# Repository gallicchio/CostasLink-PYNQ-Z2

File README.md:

# CostasLink-PYNQ-Z2

**A radio link whose reply is on its way 20 to 25 ns after the question arrives.**

An open-hardware 5 GHz transceiver board for a [PYNQ-Z2](http://www.pynq.io/boards.html), built for quantum
position verification: one station sends a challenge (a measurement basis), the other decides which of four it was
and answers, and the electronics add tens of nanoseconds to the light's travel time.

<p> </p>

Rev A on its PYNQ-Z2, and as drawn in KiCad: the front, with every jack labelled, and the back, with its
instructions. Click any image to open it at full size.

## What rev A measured

| | measured | how |
|---|---|---|
| **Turnaround**, antenna jack in to antenna jack out | **23 to 25 ns**; **20.4 to 20.8 ns** with lower thresholds | one board answering itself through a cable; no clock in the path |
| **Throughput**, idle to 1 of 4 | **2 million challenges a second** (4 Mbit/s), each answered and checked | two boards, both directions at once |
| | 4.2 million a second (8.3 Mbit/s) | one board, cabled to itself |
| **Errors**, cabled | **1 wrong in 155 billion** challenges, none missed | two boards, 21.6 hours |
| **Errors**, over the air | 1.5 in a million of 25.6 billion, in bursts | dishes across the lab one way, small antennas back, 3.6 hours untouched |
| **Idle to 1 of 8** (3 bits) | 105 million symbols, none wrong | two boards, cabled |
| **Round trip** | 120 ns on bench cables, 245 ns across the lab | one station's transmit edge to its decision on the other's reply |
| **Plain BPSK** | no error in 89 billion bits at 2 to 50 Mbaud; error-free to 20 Mbaud across the lab | one board over the air; two boards over the dishes |
| **Cost** | about $345 a board, assembled by JLCPCB | the estimate at the order, before duty and shipping; a PYNQ-Z2 is extra |

Every number is from the bench record: [`bringup/BRINGUP_LOG.md`](bringup/BRINGUP_LOG.md),
[`bringup/LATENCY.md`](bringup/LATENCY.md), [`bringup/FINDINGS.md`](bringup/FINDINGS.md).

## Photos

<table>
<tr>
<td width="50%"></td>
<td width="50%"></td>
</tr>
<tr>
<td>The two stations: a PYNQ-Z2 and a rev A board each.</td>
<td>Both stations running. Left scope: a challenge and its reply. Right scope: the received constellation, the idle and its messages.</td>
</tr>
<tr>
<td></td>
<td>One station at a demonstration in a lecture hall: a dish to send and a dish to receive, on carriers 600 MHz apart. The scope shows the live constellation.<br><br>All the photos are in <a href="photos/README.md"><code>photos/</code></a>.</td>
</tr>
</table>

## How it works

- **The transmitter never stops.** It idles on a plain carrier, so the receiver is always locked.
- **A message is one brief step** of that carrier to another point in the I/Q plane, then back.
- **A hardware Costas loop** keeps the receiver's oscillator on the carrier. It is slow (3 kHz) and the data never
  pass through it.
- **Five comparators decide**, straight off DC-coupled I and Q. No ADC, no matched filter, no symbol clock.
- **The FPGA's fast path has no clock**: comparator pins, a lookup table, transmit pins, 5 to 6 ns.

### Deciding before the symbol settles

- A receiver that samples a settled symbol waits about 1/bandwidth. This one waits for a threshold.
- With little noise the threshold sits close to the idle, and the rising edge crosses it early.
- Measured: lowering the thresholds from 0.4 to 0.2 of the step took 3 ns off the turnaround.
- The price: set too low, noise fires the comparators. In the two-board link, false events stopped at 0.4.

### Idle to 1 of N

| scheme | bits a symbol | tested |
|---|---|---|
| idle to 1 of 2 | 1 | cabled and over the air |
| **idle to 1 of 4** | 2 | cabled and over the air: most of the results above |
| **idle to 1 of 8** | 3 | cabled: 105 million symbols, none wrong |

**Eight is the most this board can do.** Two 2-bit resistor ladders give three levels on each axis, nine points:
the idle and eight messages. Four window comparators read each axis as low, middle or high. More messages need
more comparators and a linear transmitter ([`bringup/REVB.md`](bringup/REVB.md), row 42).

### Where a round trip's time goes

## What rev A does not do

| limit | detail |
|---|---|
| **5.8 GHz** | Designed for the 5.8 GHz band, but the receive gain falls off above 4.5 GHz and no link closed at 5.8. Every result here is on carriers between 4.4 and 5.5 GHz. |
| **A decoded message on a pin** | 85 to 105 ns one way, about 80 ns of it the gateware's clocked pipeline. The 20 to 25 ns is the clockless reply. |
| **One antenna** | Both directions at once need two antennas a board and carriers 600 MHz apart. |
| **Distance** | The longest paths so far: about 16 m of air across a lab, and a lecture hall. |
| **Lock** | Software restores a lost lock in 2 to 3 s. The thresholds are set for one signal level, within about 6 dB. |
| **1 of 8** | Tested over cables only. |

The full list, each with its measurement: [`bringup/REVB.md`](bringup/REVB.md).

## What is here

| path | what |
|---|---|
| [`hardware/`](hardware/) | the KiCad 10 project: 120 x 100 mm, 4 layers |
| [`mfg/release/`](mfg/release/) | what was uploaded to JLCPCB: Gerbers, BOM, placement |
| [`gateware/`](gateware/README.md) | the Verilog, the PYNQ overlay's build, the Python driver |
| [`bringup/`](bringup/README.md) | the bench programs, the log of every measurement, the list for rev B |
| [`gen/`](gen/), [`sim/`](sim/), [`tools/`](tools/) | the scripts that generate and check the design (`python3 build.py`) |
| [`docs/`](docs/) | the schematic as [PDF](docs/images/CostasLink-PYNQ-Z2_schematic.pdf), the studies, the figures |
| [`PLAN.md`](PLAN.md), [`BRINGUP.md`](BRINGUP.md) | the design and its reasons; the bring-up procedure |
| [`docs/DESIGN_STATUS.md`](docs/DESIGN_STATUS.md) | the design phase's own summary, step by step |
| [`design_review/`](design_review/README.md) | six reviews before the order, and [what was done about them](DESIGN_REVIEW_RESPONSE.md) |
| [`photos/`](photos/README.md) | the boards and the bench |

## How it was made

Jason Gallicchio designed this with Claude (Anthropic's Fable 5.1 and Opus 5.5, in Claude Code).

| | dates | days |
|---|---|---|
| Design, to the order at JLCPCB | 2026-10-09 to 2026-10-17 | 9 |
| Boards delivered | 2026-10-28 | |
| Bring-up and debugging | 2026-10-28 to 2026-11-11 | 15 |

Every prompt and every response is kept: [`CLAUDE_CODE_CHAT.md`](CLAUDE_CODE_CHAT.md) for the design,
[`bringup/CLAUDE_CODE_CHAT_BRINGUP.md`](bringup/CLAUDE_CODE_CHAT_BRINGUP.md) for the bench.

The board grew up in a private repository of the research group. Its commits are all here; vendor datasheets
are not. Commit hashes quoted in the documents are the old ones: [`docs/COMMIT_MAP.tsv`](docs/COMMIT_MAP.tsv).

## Before you transmit

This is an uncertified experimental radio. Check what you are licensed to radiate where you are, or work over
cables.

## Licence

Hardware under CERN-OHL-P-2.0, software under MIT: [`LICENSE`](LICENSE).

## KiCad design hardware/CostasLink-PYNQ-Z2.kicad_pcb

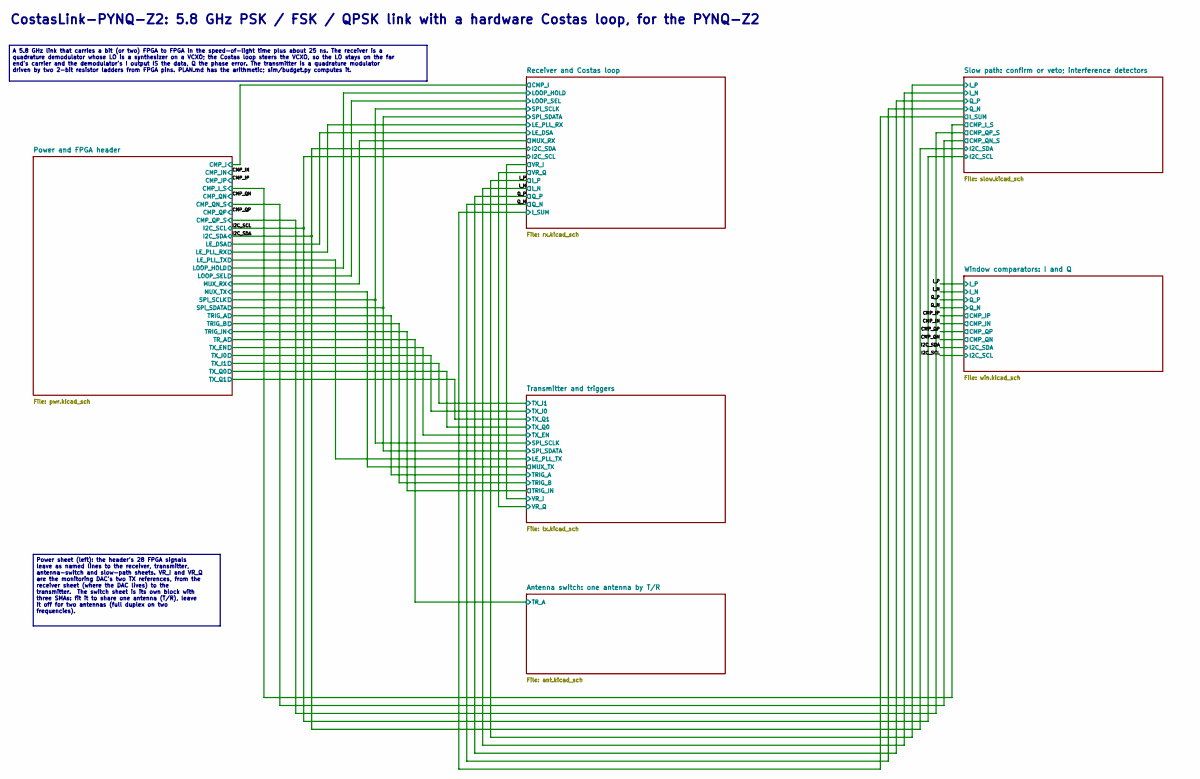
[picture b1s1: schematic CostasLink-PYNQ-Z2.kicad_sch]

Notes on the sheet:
CostasLink-PYNQ-Z2: 5.8 GHz PSK / FSK / QPSK link with a hardware Costas loop, for the PYNQ-Z2
A 5.8 GHz link that carries a bit (or two) FPGA to FPGA in the speed-of-light time plus about 25 ns. The receiver is a quadrature demodulator whose LO is a synthesizer on a VCXO; the Costas loop steers the VCXO, so the LO stays on the far end's carrier and the demodulator's I output IS the data, Q 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
Power sheet (left): the header's 28 FPGA signals leave as named lines to the receiver, transmitter, antenna-switch and slow-path sheets. VR_I and VR_Q are the monitoring DAC's two TX references, from the receiver sheet (where the DAC lives) to the transmitter. The switch sheet is its own block with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

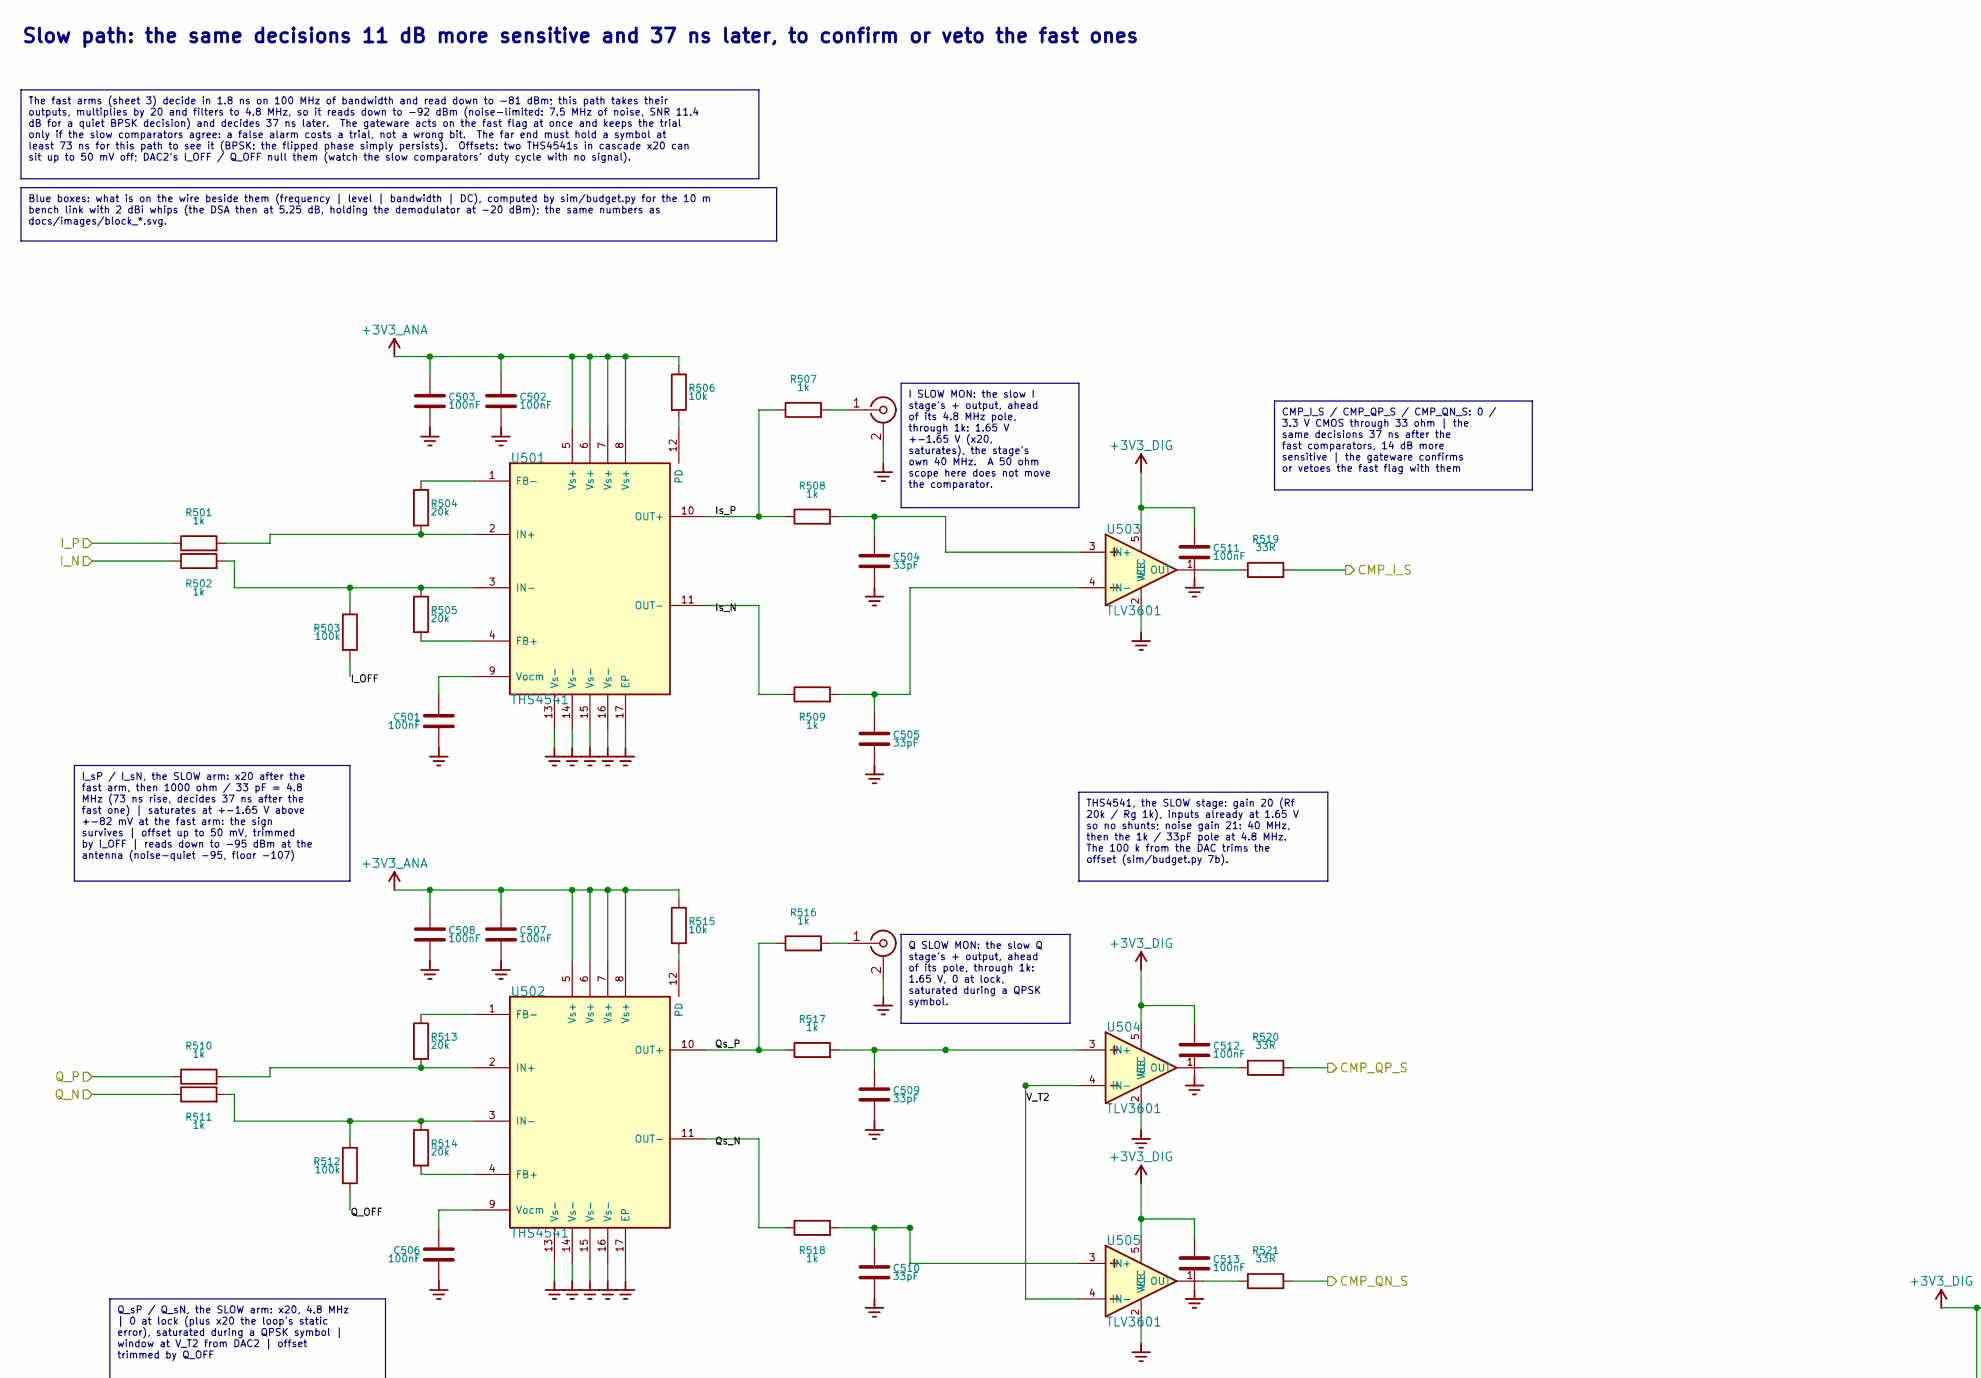
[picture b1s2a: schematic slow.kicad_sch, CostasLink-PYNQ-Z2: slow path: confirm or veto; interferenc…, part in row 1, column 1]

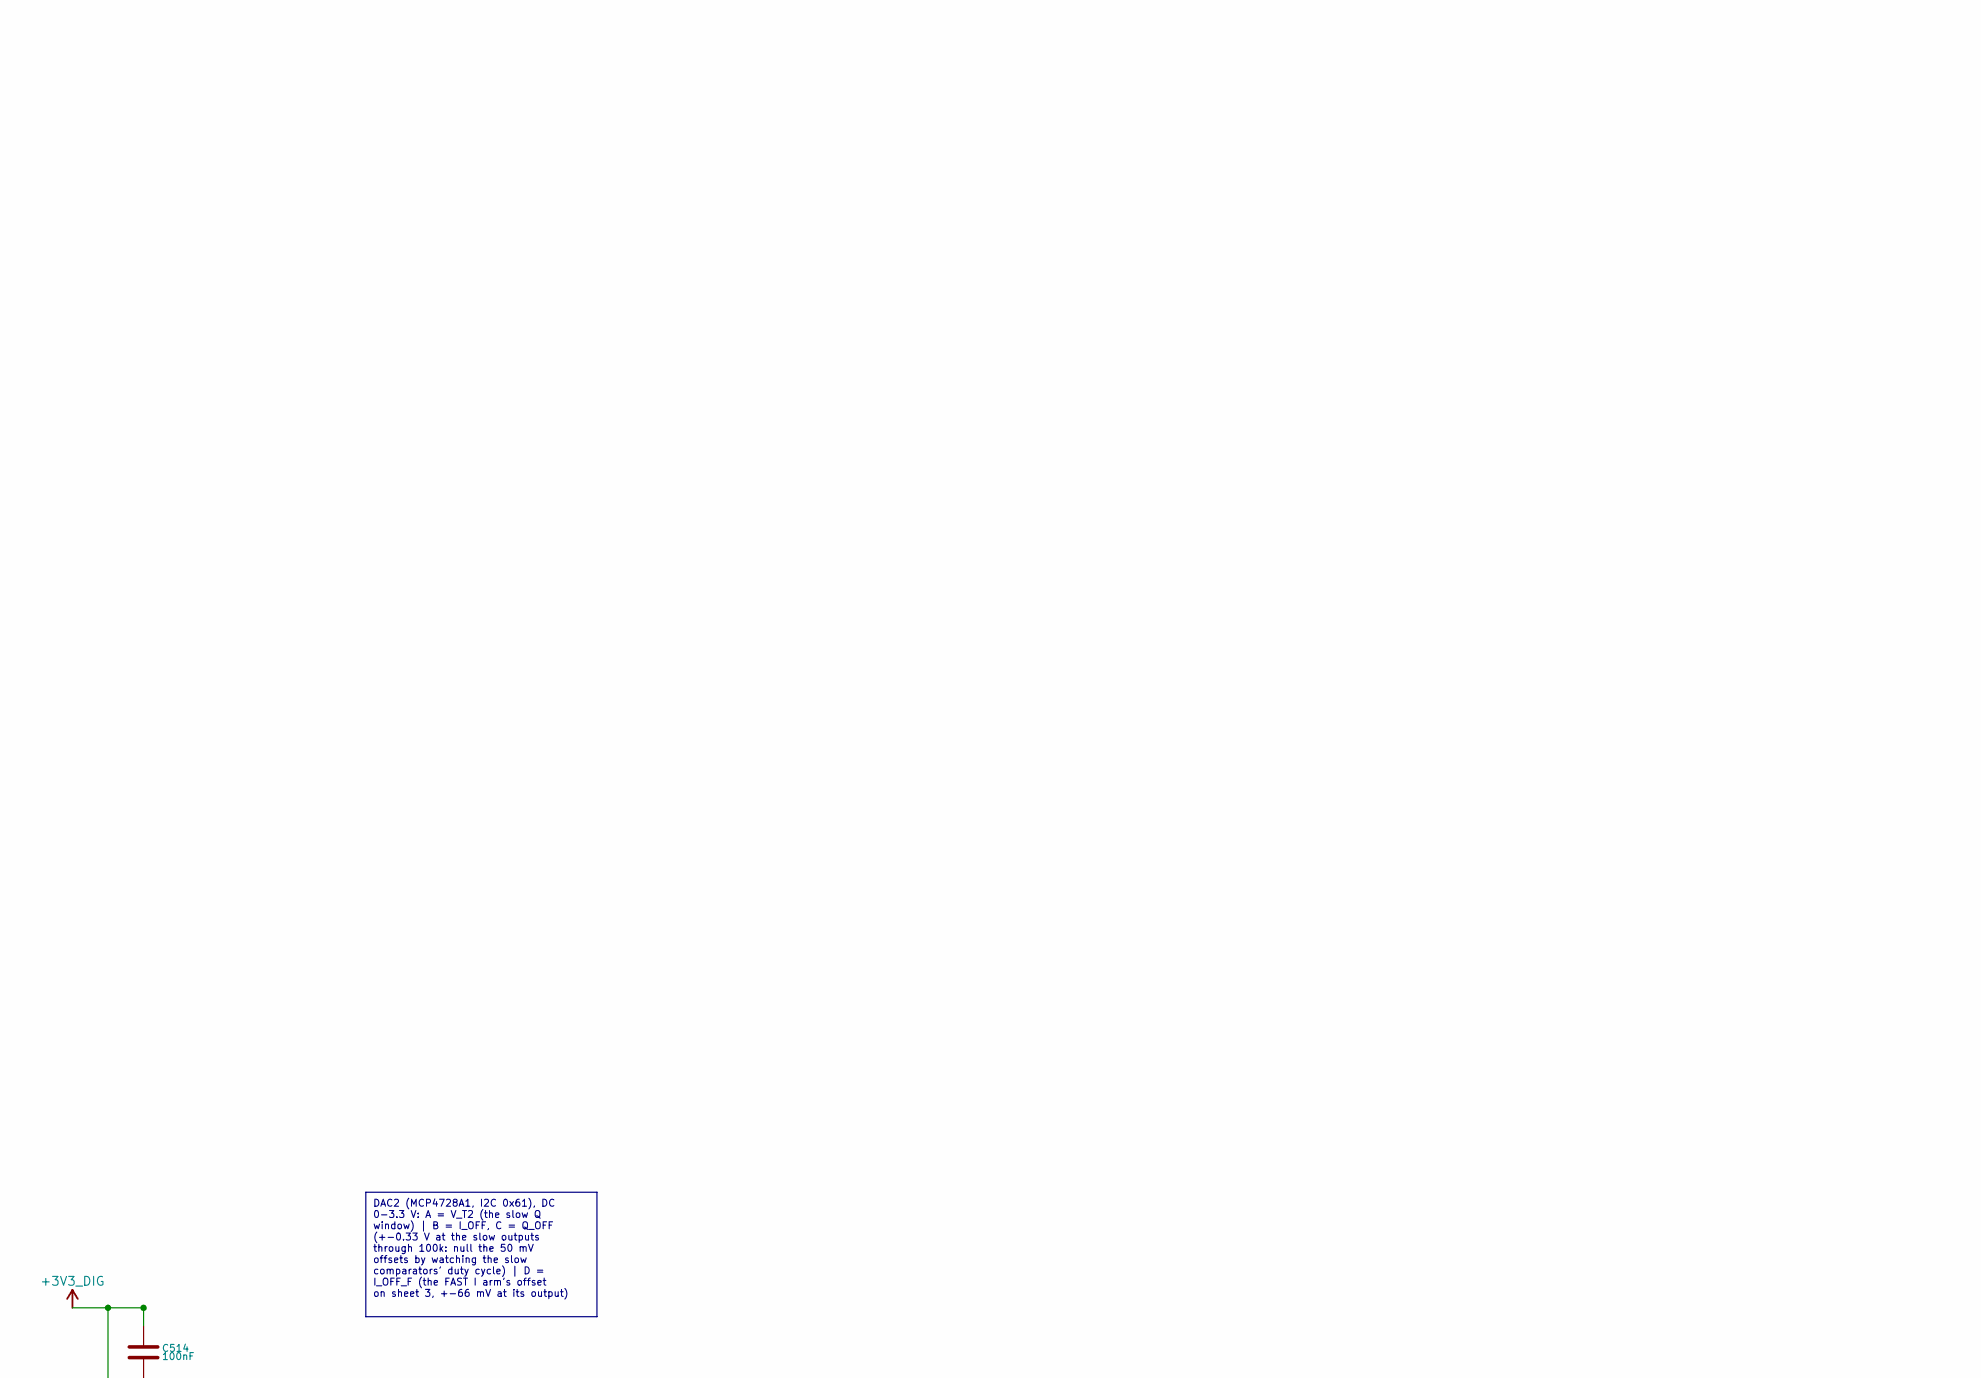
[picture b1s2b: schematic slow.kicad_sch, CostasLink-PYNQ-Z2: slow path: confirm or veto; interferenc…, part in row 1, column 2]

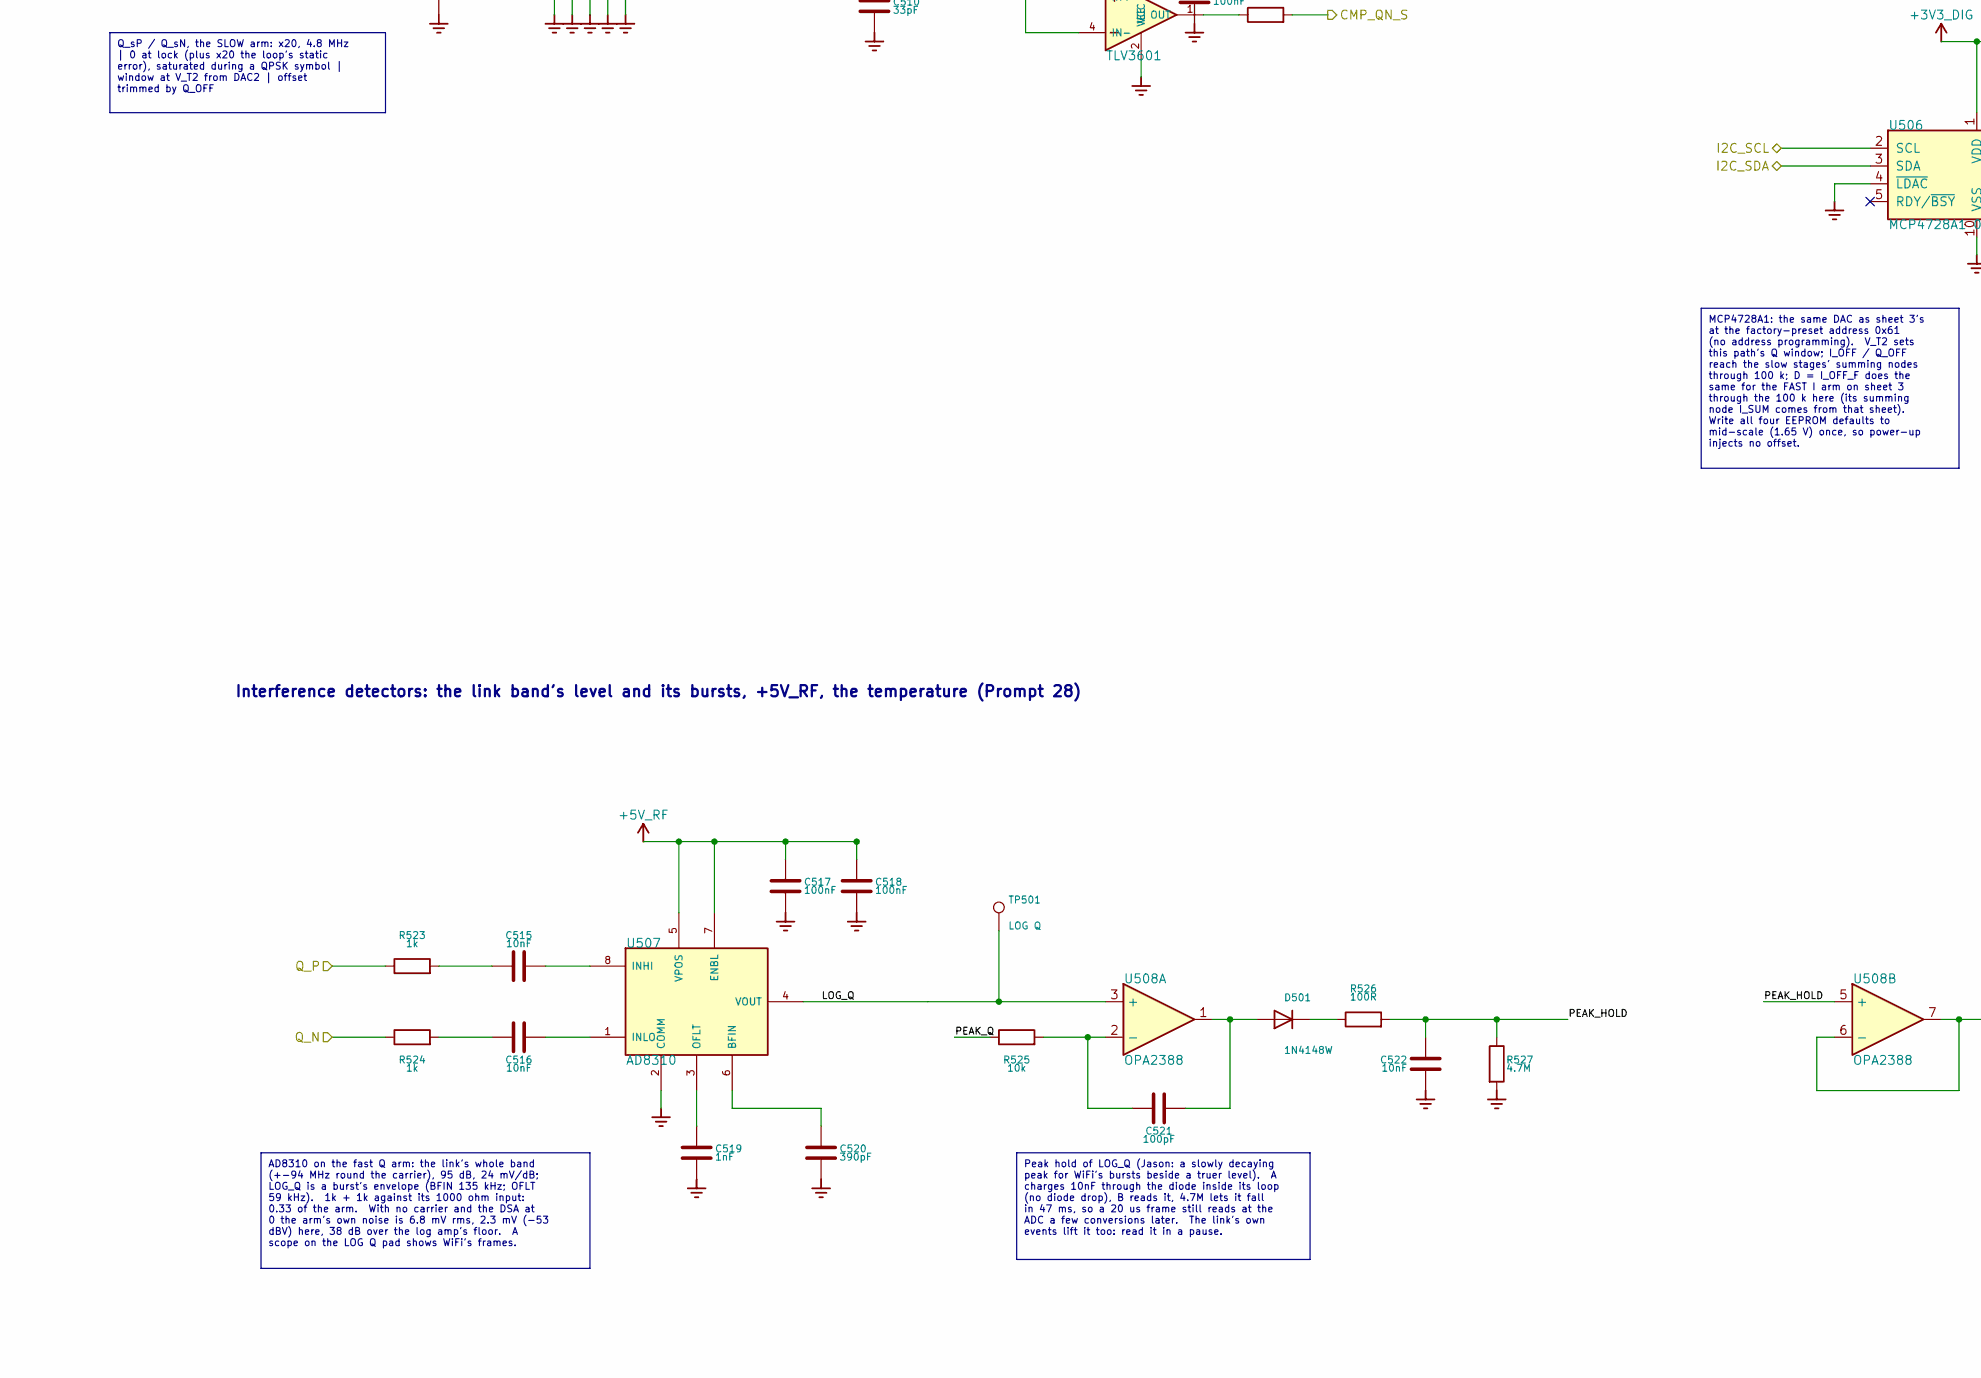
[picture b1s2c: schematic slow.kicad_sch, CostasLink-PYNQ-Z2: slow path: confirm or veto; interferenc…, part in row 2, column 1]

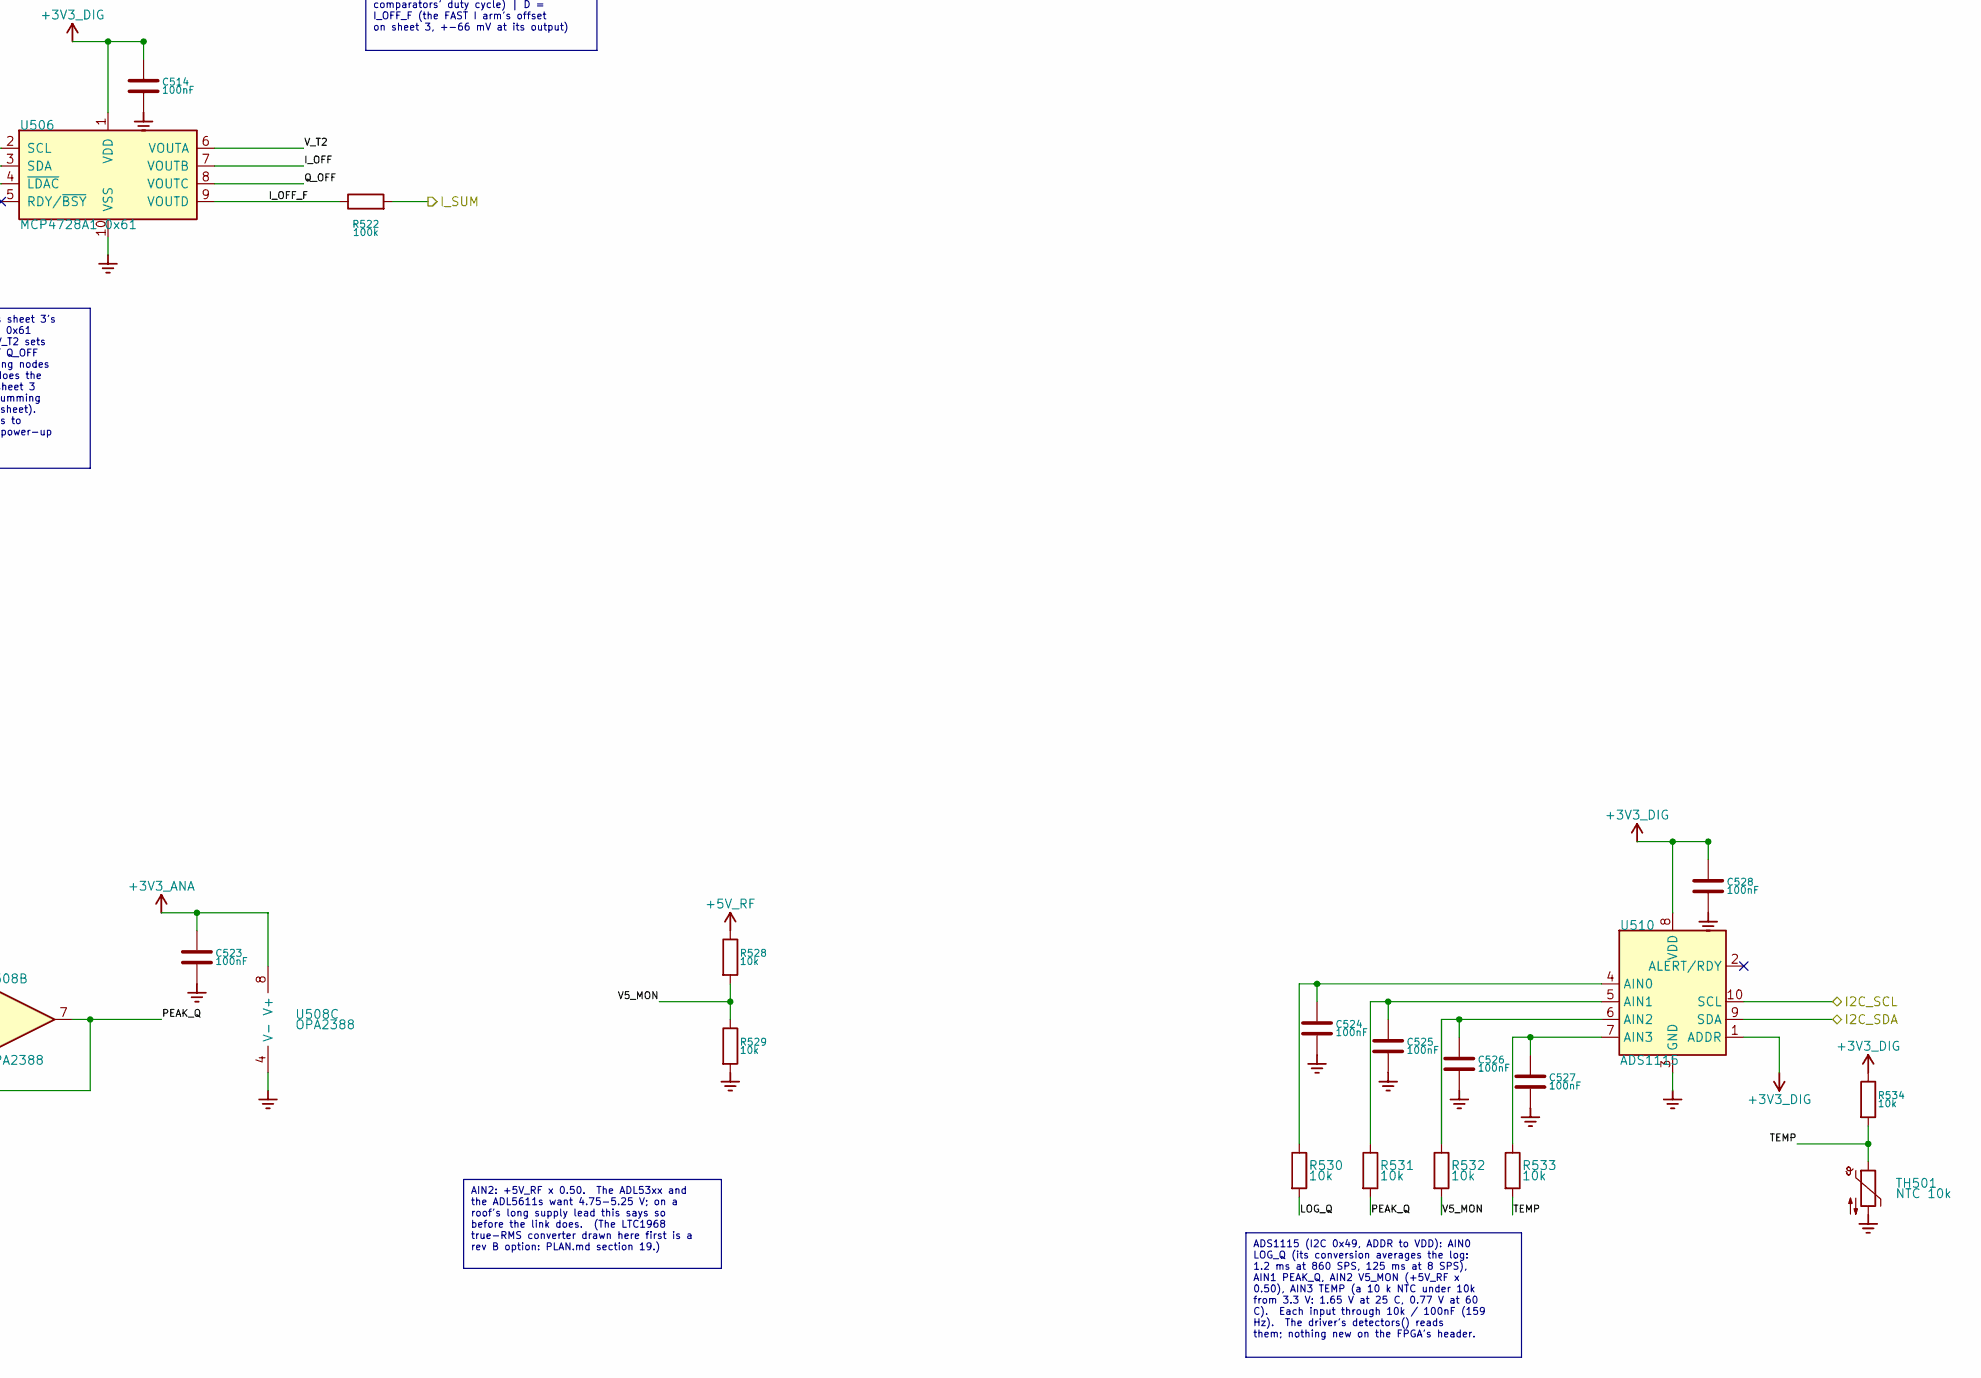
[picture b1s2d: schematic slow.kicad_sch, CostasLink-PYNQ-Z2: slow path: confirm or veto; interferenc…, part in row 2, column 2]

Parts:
C501, C502, C503, C506, C507, C508, C511, C512, C513, C514, C517, C518, C523, C524, C525, C526, C527, C528: 100nF; C_0402_1005Metric; MPN CL05B104KO5NNNC; LCSC C1525
C504, C505, C509, C510: 33pF; C_0402_1005Metric; MPN 0402CG330J500NT; LCSC C1562
C515, C516, C522: 10nF; C_0402_1005Metric; MPN CL05B103KB5NNNC; LCSC C15195
C519: 1nF; C_0402_1005Metric; MPN 0402B102K500NT; LCSC C1523
C520: 390pF; C_0402_1005Metric; MPN CC0402JRNPO9BN391; LCSC C282239
C521: 100pF; C_0402_1005Metric; MPN 0402CG101J500NT; LCSC C1546
D501: 1N4148W; D_SOD-123; MPN 1N4148W; LCSC C81598
J501: I SLOW MON; MMCX_BWMMCX-KE_Vertical; MPN BWMMCX-KE; LCSC C5137198
J502: Q SLOW MON; U.FL_Hirose_U.FL-R-SMT-1_Vertical; MPN U.FL-R-SMT-1(80); LCSC C88374
R501, R502, R507, R508, R509, R510, R511, R516, R517, R518, R523, R524: 1k; R_0402_1005Metric; MPN 0402WGF1001TCE; LCSC C11702
R503, R512, R522: 100k; R_0402_1005Metric; MPN 0402WGF1003TCE; LCSC C25741
R504, R505, R513, R514: 20k; R_0402_1005Metric; MPN 0402WGF2002TCE; LCSC C25765
R506, R515, R525, R528, R529, R530, R531, R532, R533, R534: 10k; R_0402_1005Metric; MPN 0402WGF1002TCE; LCSC C25744
R519, R520, R521: 33R; R_0402_1005Metric; MPN 0402WGF330JTCE; LCSC C25105
R526: 100R; R_0402_1005Metric; MPN 0402WGF1000TCE; LCSC C25076
R527: 4.7M; R_0402_1005Metric; MPN 0402WGF4704TCE; LCSC C474132
TH501: NTC 10k; R_0603_1608Metric; MPN NCP18XH103F03RB; LCSC C13564
TP501: LOG Q; TestPoint_Pad_D1.5mm
U501, U502: THS4541; VQFN-16-1EP_3x3mm_P0.5mm_EP1.68x1.68mm; MPN THS4541IRGTT; LCSC C2058382
U503, U504, U505: TLV3601; SOT-353_SC-70-5; MPN TLV3601DCKR; LCSC C2974371
U506: MCP4728A1 0x61; MSOP-10_3x3mm_P0.5mm; MPN MCP4728A1T-E/UN; LCSC C627342
U507: AD8310; MSOP-8_3x3mm_P0.65mm; MPN AD8310ARMZ-REEL7; LCSC C42711
U508: OPA2388; VSSOP-8_3x3mm_P0.65mm; MPN OPA2388IDGKR; LCSC C2059281
U510: ADS1115; TSSOP-10_3x3mm_P0.5mm; MPN ADS1115IDGSR; LCSC C37593

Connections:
+3V3_ANA: C502.1, C503.1, C507.1, C508.1, C523.1, R506.1, R515.1, U501.5 (Vs+), U501.6 (Vs+), U501.7 (Vs+), U501.8 (Vs+), U502.5 (Vs+), U502.6 (Vs+), U502.7 (Vs+), U502.8 (Vs+), U508.8 (V+); also elsewhere on the board
+3V3_DIG: C511.1, C512.1, C513.1, C514.1, C528.1, R534.1, U503.5 (VCC), U504.5 (VCC), U505.5 (VCC), U506.1 (VDD), U510.1 (ADDR), U510.8 (VDD); also elsewhere on the board
+5V_RF: C517.1, C518.1, R528.1, U507.5 (VPOS), U507.7 (ENBL); also elsewhere on the board
/I2C_SCL: U506.2 (SCL), U510.10 (SCL); also elsewhere on the board
/I2C_SDA: U506.3 (SDA), U510.9 (SDA); also elsewhere on the board
/I_N: R502.1; also elsewhere on the board
/I_P: R501.1; also elsewhere on the board
/Power and FPGA header/CMP_I_S: R519.2; also elsewhere on the board
/Power and FPGA header/CMP_QN_S: R521.2; also elsewhere on the board
/Power and FPGA header/CMP_QP_S: R520.2; also elsewhere on the board
/Q_N: R511.1, R524.1; also elsewhere on the board
/Q_P: R510.1, R523.1; also elsewhere on the board
/Receiver and Costas loop/I_SUM: R522.2; also elsewhere on the board
/Slow path: confirm or veto; interference detectors/I_OFF: R503.2, U506.7 (VOUTB)
/Slow path: confirm or veto; interference detectors/I_OFF_F: R522.1, U506.9 (VOUTD)
/Slow path: confirm or veto; interference detectors/Is_N: R509.1, U501.11 (OUT-)
/Slow path: confirm or veto; interference detectors/Is_P: R507.1, R508.1, U501.10 (OUT+)
/Slow path: confirm or veto; interference detectors/LOG_Q: R530.2, TP501.1, U507.4 (VOUT), U508.3 (+)
/Slow path: confirm or veto; interference detectors/PEAK_HOLD: C522.1, R526.2, R527.1, U508.5 (+)
/Slow path: confirm or veto; interference detectors/PEAK_Q: R525.1, R531.2, U508.6 (-), U508.7
/Slow path: confirm or veto; interference detectors/Q_OFF: R512.2, U506.8 (VOUTC)
/Slow path: confirm or veto; interference detectors/Qs_N: R518.1, U502.11 (OUT-)
/Slow path: confirm or veto; interference detectors/Qs_P: R516.1, R517.1, U502.10 (OUT+)
/Slow path: confirm or veto; interference detectors/TEMP: R533.2, R534.2, TH501.1
/Slow path: confirm or veto; interference detectors/V5_MON: R528.2, R529.1, R532.2
/Slow path: confirm or veto; interference detectors/V_T2: U504.4 (IN-), U505.4 (IN-), U506.6 (VOUTA)
unnamed: C515.1, R523.2
unnamed: C516.1, R524.2
unnamed: C521.2, D501.2 (A), U508.1
unnamed: D501.1 (K), R526.1
unnamed: J501.1 (In), R507.2
unnamed: J502.1 (In), R516.2
unnamed: R505.2, U501.4 (FB+)
unnamed: R504.1, U501.1 (FB-)
unnamed: R501.2, R504.2, U501.2 (IN+)
unnamed: R502.2, R503.1, R505.1, U501.3 (IN-)
unnamed: R506.2, U501.12 (PD)
unnamed: C501.1, U501.9 (Vocm)
unnamed: R514.2, U502.4 (FB+)
unnamed: R513.1, U502.1 (FB-)
unnamed: R510.2, R513.2, U502.2 (IN+)
unnamed: R511.2, R512.1, R514.1, U502.3 (IN-)
unnamed: R515.2, U502.12 (PD)
unnamed: C506.1, U502.9 (Vocm)
unnamed: C504.1, R508.2, U503.3 (IN+)
unnamed: C505.1, R509.2, U503.4 (IN-)
unnamed: R519.1, U503.1 (OUT)
unnamed: C509.1, R517.2, U504.3 (IN+)
unnamed: R520.1, U504.1 (OUT)
unnamed: C510.1, R518.2, U505.3 (IN+)
unnamed: R521.1, U505.1 (OUT)
unnamed: C520.1, U507.6 (BFIN)
unnamed: C515.2, U507.8 (INHI)
unnamed: C516.2, U507.1 (INLO)
unnamed: C519.1, U507.3 (OFLT)
unnamed: C521.1, R525.2, U508.2 (-)
unnamed: C524.1, R530.1, U510.4 (AIN0)
unnamed: C525.1, R531.1, U510.5 (AIN1)
unnamed: C526.1, R532.1, U510.6 (AIN2)
unnamed: C527.1, R533.1, U510.7 (AIN3)

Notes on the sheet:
Slow path: the same decisions 11 dB more sensitive and 37 ns later, to confirm or veto the fast ones
Interference detectors: the link band's level and its bursts, +5V_RF, the temperature (Prompt 28)
The fast arms (sheet 3) decide in 1.8 ns on 100 MHz of bandwidth and read down to -81 dBm; this path takes their outputs, multiplies by 20 and filters to 4.8 MHz, so it reads down to -92 dBm (noise-limited: 7.5 MHz of noise, SNR 11.4 dB for a quiet BPSK decision) and decides 37 ns later. The gatewa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
Blue boxes: what is on the wire beside them (frequency | level | bandwidth | DC), computed by sim/budget.py for the 10 m bench link with 2 dBi whips (the DSA then at 5.25 dB, holding the demodulator at -20 dBm); the same numbers as docs/images/block_*.svg.
I SLOW MON: the slow I stage's + output, ahead of its 4.8 MHz pole, through 1k: 1.65 V +-1.65 V (x20, saturates), the stage's own 40 MHz. A 50 ohm scope here does not move the comparator.
I_sP / I_sN, the SLOW arm: x20 after the fast arm, then 1000 ohm / 33 pF = 4.8 MHz (73 ns rise, decides 37 ns after the fast one) | saturates at +-1.65 V above +-82 mV at the fast arm: the sign survives | offset up to 50 mV, trimmed by I_OFF | reads down to -95 dBm at the antenna (noise-quiet -95, 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
Q SLOW MON: the slow Q stage's + output, ahead of its pole, through 1k: 1.65 V, 0 at lock, saturated during a QPSK symbol.
Q_sP / Q_sN, the SLOW arm: x20, 4.8 MHz | 0 at lock (plus x20 the loop's static error), saturated during a QPSK symbol | window at V_T2 from DAC2 | offset trimmed by Q_OFF
THS4541, the SLOW stage: gain 20 (Rf 20k / Rg 1k), inputs already at 1.65 V so no shunts; noise gain 21: 40 MHz, then the 1k / 33pF pole at 4.8 MHz. The 100 k from the DAC trims the offset (sim/budget.py 7b).
CMP_I_S / CMP_QP_S / CMP_QN_S: 0 / 3.3 V CMOS through 33 ohm | the same decisions 37 ns after the fast comparators, 14 dB more sensitive | the gateware confirms or vetoes the fast flag with them
DAC2 (MCP4728A1, I2C 0x61), DC 0-3.3 V: A = V_T2 (the slow Q window) | B = I_OFF, C = Q_OFF (+-0.33 V at the slow outputs through 100k: null the 50 mV offsets by watching the slow comparators' duty cycle) | D = I_OFF_F (the FAST I arm's offset on sheet 3, +-66 mV at its output)
MCP4728A1: the same DAC as sheet 3's at the factory-preset address 0x61 (no address programming). V_T2 sets this path's Q window; I_OFF / Q_OFF reach the slow stages' summing nodes through 100 k; D = I_OFF_F does the same for the FAST I arm on sheet 3 through the 100 k here (its summing node I_SUM 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
AD8310 on the fast Q arm: the link's whole band (+-94 MHz round the carrier), 95 dB, 24 mV/dB; LOG_Q is a burst's envelope (BFIN 135 kHz; OFLT 59 kHz). 1k + 1k against its 1000 ohm input: 0.33 of the arm. With no carrier and the DSA at 0 the arm's own noise is 6.8 mV rms, 2.3 mV (-53 dBV) here, 38 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
Peak hold of LOG_Q (Jason: a slowly decaying peak for WiFi's bursts beside a truer level). A charges 10nF through the diode inside its loop (no diode drop), B reads it, 4.7M lets it fall in 47 ms, so a 20 us frame still reads at the ADC a few conversions later. The link's own events lift it too: re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
AIN2: +5V_RF x 0.50. The ADL53xx and the ADL5611s want 4.75-5.25 V; on a roof's long supply lead this says so before the link does. (The LTC1968 true-RMS converter drawn here first is a rev B option: PLAN.md section 19.)
ADS1115 (I2C 0x49, ADDR to VDD): AIN0 LOG_Q (its conversion averages the log: 1.2 ms at 860 SPS, 125 ms at 8 SPS), AIN1 PEAK_Q, AIN2 V5_MON (+5V_RF x 0.50), AIN3 TEMP (a 10 k NTC under 10k from 3.3 V: 1.65 V at 25 C, 0.77 V at 60 C). Each input through 10k / 100nF (159 Hz). The driver's detectors()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

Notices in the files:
hardware/CostasLink-PYNQ-Z2.kicad_sch:
Hardware CERN-OHL-P-2.0, software MIT
